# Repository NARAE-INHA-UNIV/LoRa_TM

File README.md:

# LoRa TM

DIY telemetry module based Ebyte LoRa.

- 활동명 : [UAV] DIY Telemerty Module
- 일시 : 2024 동계방학
- 팀명 : 항공전자 (구 FC)
- 팀장 : 
  - 송민우 (2024) : 개념 설계, 회로 설계
  - 이현제 (2025) : 회로 설계, 펌웨어 작성

## USB CDC

ST에서 제공하는 라이브러리 사용시 RAM, Flash memory 용량 초과.

[Making USB Device With STM32 + TinyUSB](https://ejaaskel.dev/making-usb-device-with-stm32-tinyusb/)

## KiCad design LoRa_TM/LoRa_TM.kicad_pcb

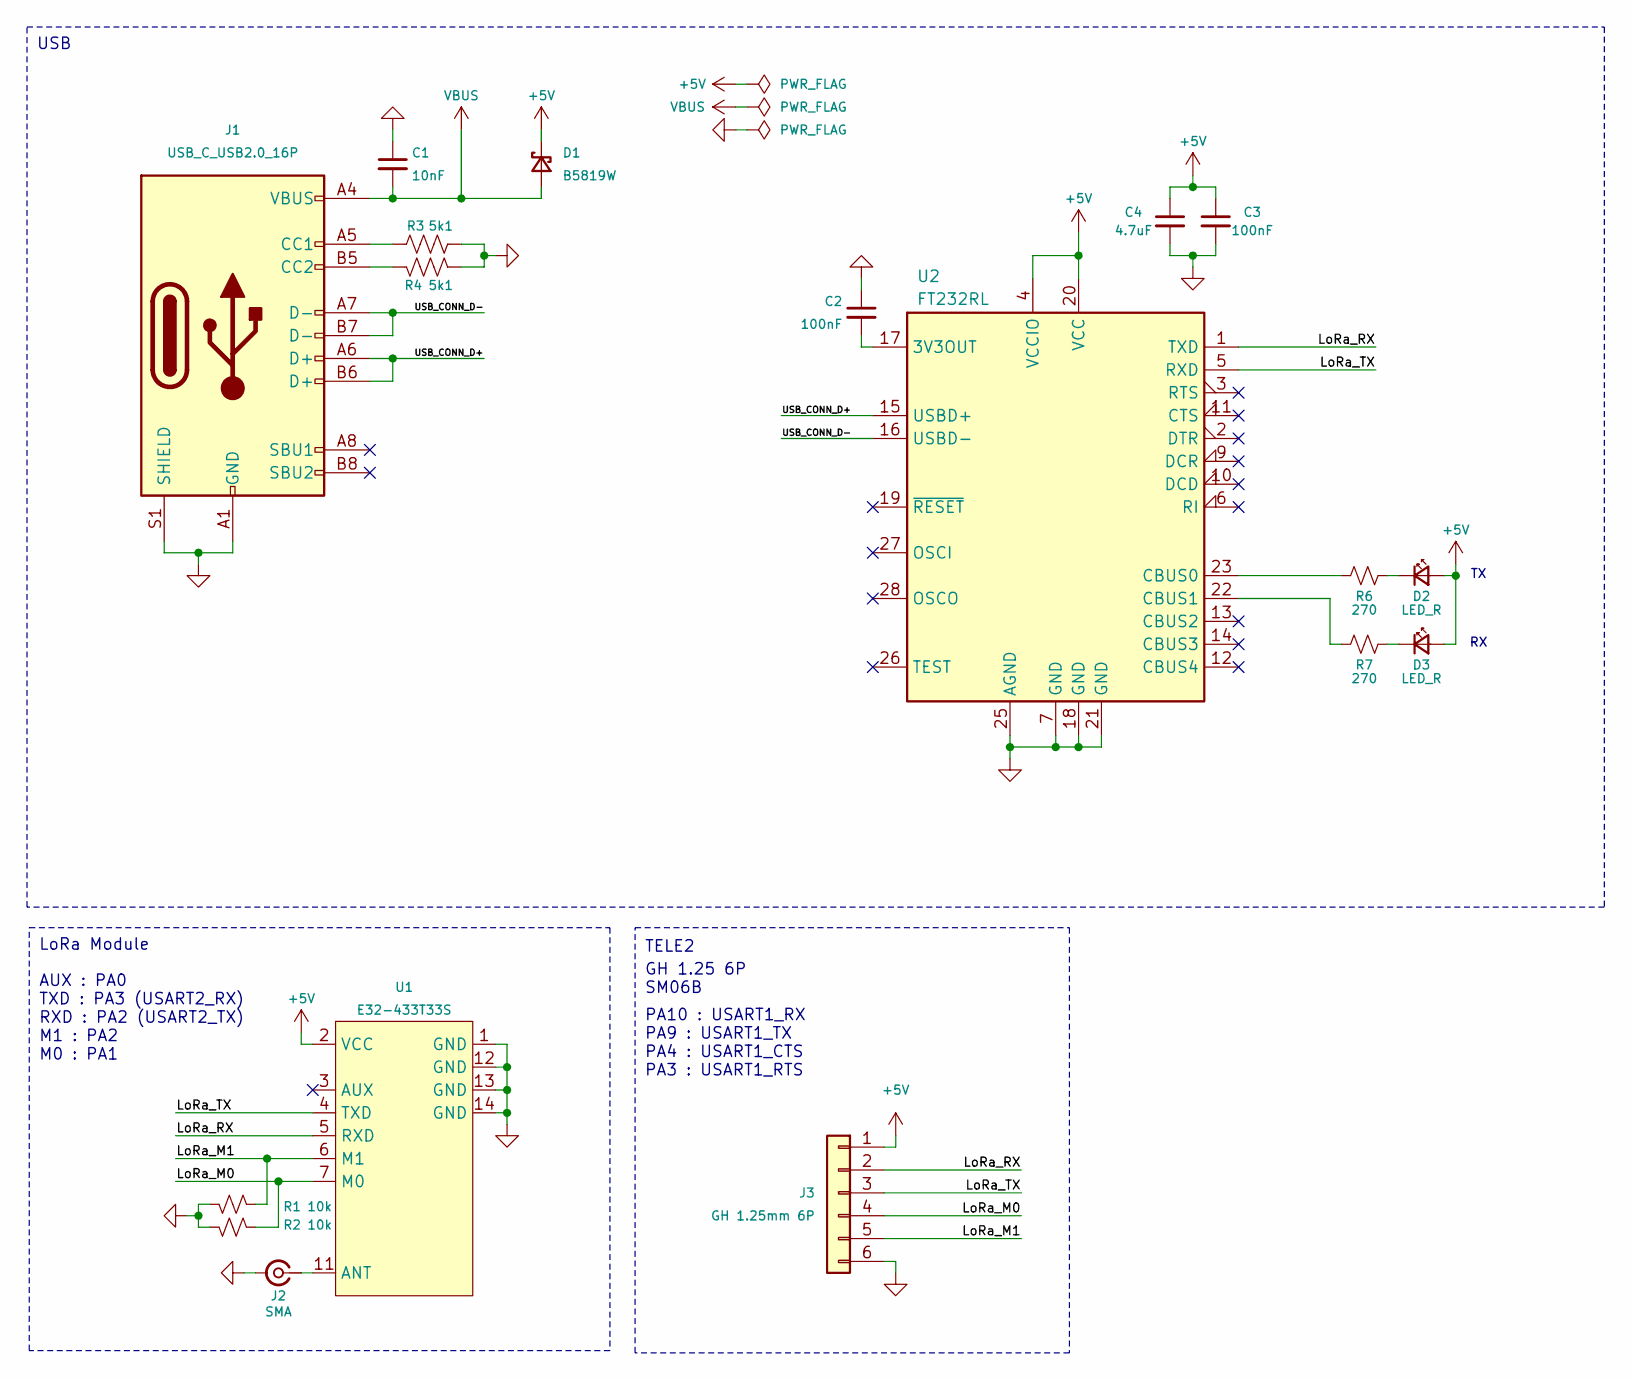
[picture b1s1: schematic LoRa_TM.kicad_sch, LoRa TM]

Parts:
C1: 10nF; C_0603_1608Metric; LCSC C1589
C2, C3: 100nF; C_0603_1608Metric; LCSC C1590
C4: 4.7uF; C_0603_1608Metric; LCSC C1705
D1: B5819W; D_SOD-323; LCSC C64885
D2, D3: LED_R; LED_0603_1608Metric; LCSC C2286
J1: USB_C_USB2.0_16P; USB_C_Receptacle_GCT_USB4105-xx-A_16P_TopMnt_Horizontal; LCSC C2765186
J2: SMA; SMA_EdgeMount; LCSC C376663
J3: GH 1.25mm 6P; JST_GH_SM06B-GHS-TB_06x1.25mm_Angled; LCSC C133065
R1, R2: 10k; R_0603_1608Metric; LCSC C15401
R3, R4: 5k1; R_0603_1608Metric; LCSC C14677
R6, R7: 270; R_0603_1608Metric; LCSC C22966
U1: E32-433T33S; E22-XXXT33S
U2: FT232RL; SSOP-28_5.3x10.2mm_P0.65mm; LCSC C8690

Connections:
+5V: C3.1, C4.1, D1.1 (K), D2.2 (A), D3.2 (A), J3.1, U1.2 (VCC), U2.4 (VCCIO), U2.20 (VCC)
/LoRa_M0: J3.4, R2.1, U1.7 (M0)
/LoRa_M1: J3.5, R1.1, U1.6 (M1)
/LoRa_RX: J3.2, U1.5 (RXD), U2.1 (TXD)
/LoRa_TX: J3.3, U1.4 (TXD), U2.5 (RXD)
/USB_CONN_D+: J1.A6 (D+), J1.B6 (D+), U2.15 (USBD+)
/USB_CONN_D-: J1.A7 (D-), J1.B7 (D-), U2.16 (USBD-)
GND: C1.1, C2.1, C3.2, C4.2, J1.A1 (GND), J1.A12 (GND), J1.B1 (GND), J1.B12 (GND), J1.S1 (SHIELD), J2.2 (Ext), J3.6, R1.2, R2.2, R3.2, R4.2, U1.1 (GND), U1.12 (GND), U1.13 (GND), U1.14 (GND), U2.7 (GND), U2.18 (GND), U2.21 (GND), U2.25 (AGND)
unnamed: D2.1 (K), R6.1
unnamed: D3.1 (K), R7.1
unnamed: J1.A5 (CC1), R3.1
unnamed: J1.B5 (CC2), R4.1
unnamed: J2.1 (In), U1.11 (ANT)
unnamed: C2.2, U2.17 (3V3OUT)
unnamed: R6.2, U2.23 (CBUS0)
unnamed: R7.2, U2.22 (CBUS1)
VBUS: C1.2, D1.2 (A), J1.A4 (VBUS), J1.A9 (VBUS), J1.B4 (VBUS), J1.B9 (VBUS)

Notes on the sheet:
TELE2
AUX : PA0 TXD : PA3 (USART2_RX) RXD : PA2 (USART2_TX) M1 : PA2 M0 : PA1
GH 1.25 6P SM06B
USB
PA10 : USART1_RX PA9 : USART1_TX PA4 : USART1_CTS PA3 : USART1_RTS
LoRa Module

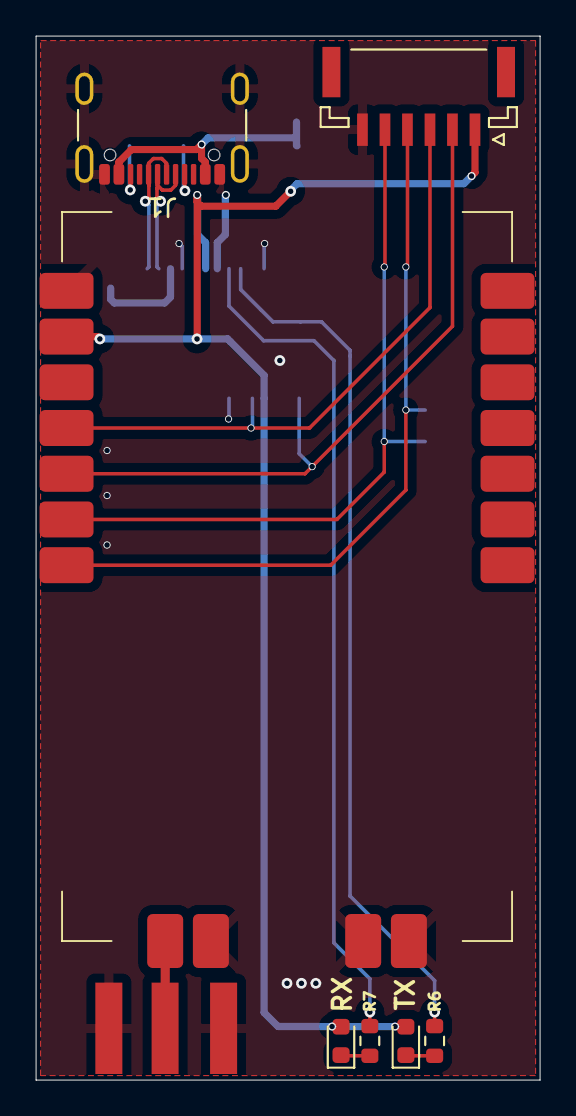
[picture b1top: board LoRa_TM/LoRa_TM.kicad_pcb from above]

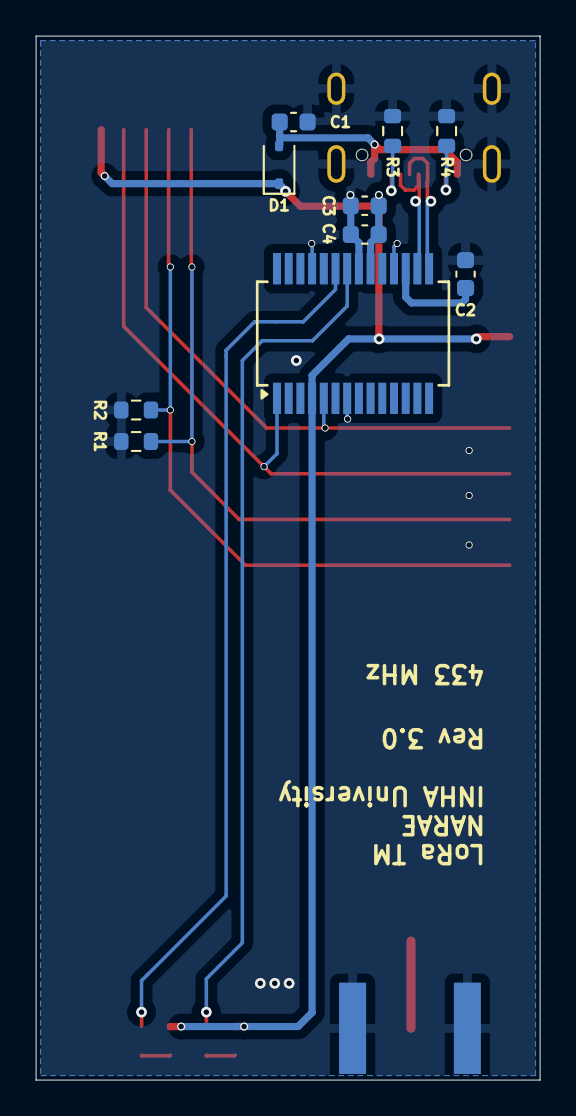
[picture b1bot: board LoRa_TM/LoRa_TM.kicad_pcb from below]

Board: 2 copper layers, 28.0 x 58.0 mm, 18 parts (10 on the bottom side), 17 nets.

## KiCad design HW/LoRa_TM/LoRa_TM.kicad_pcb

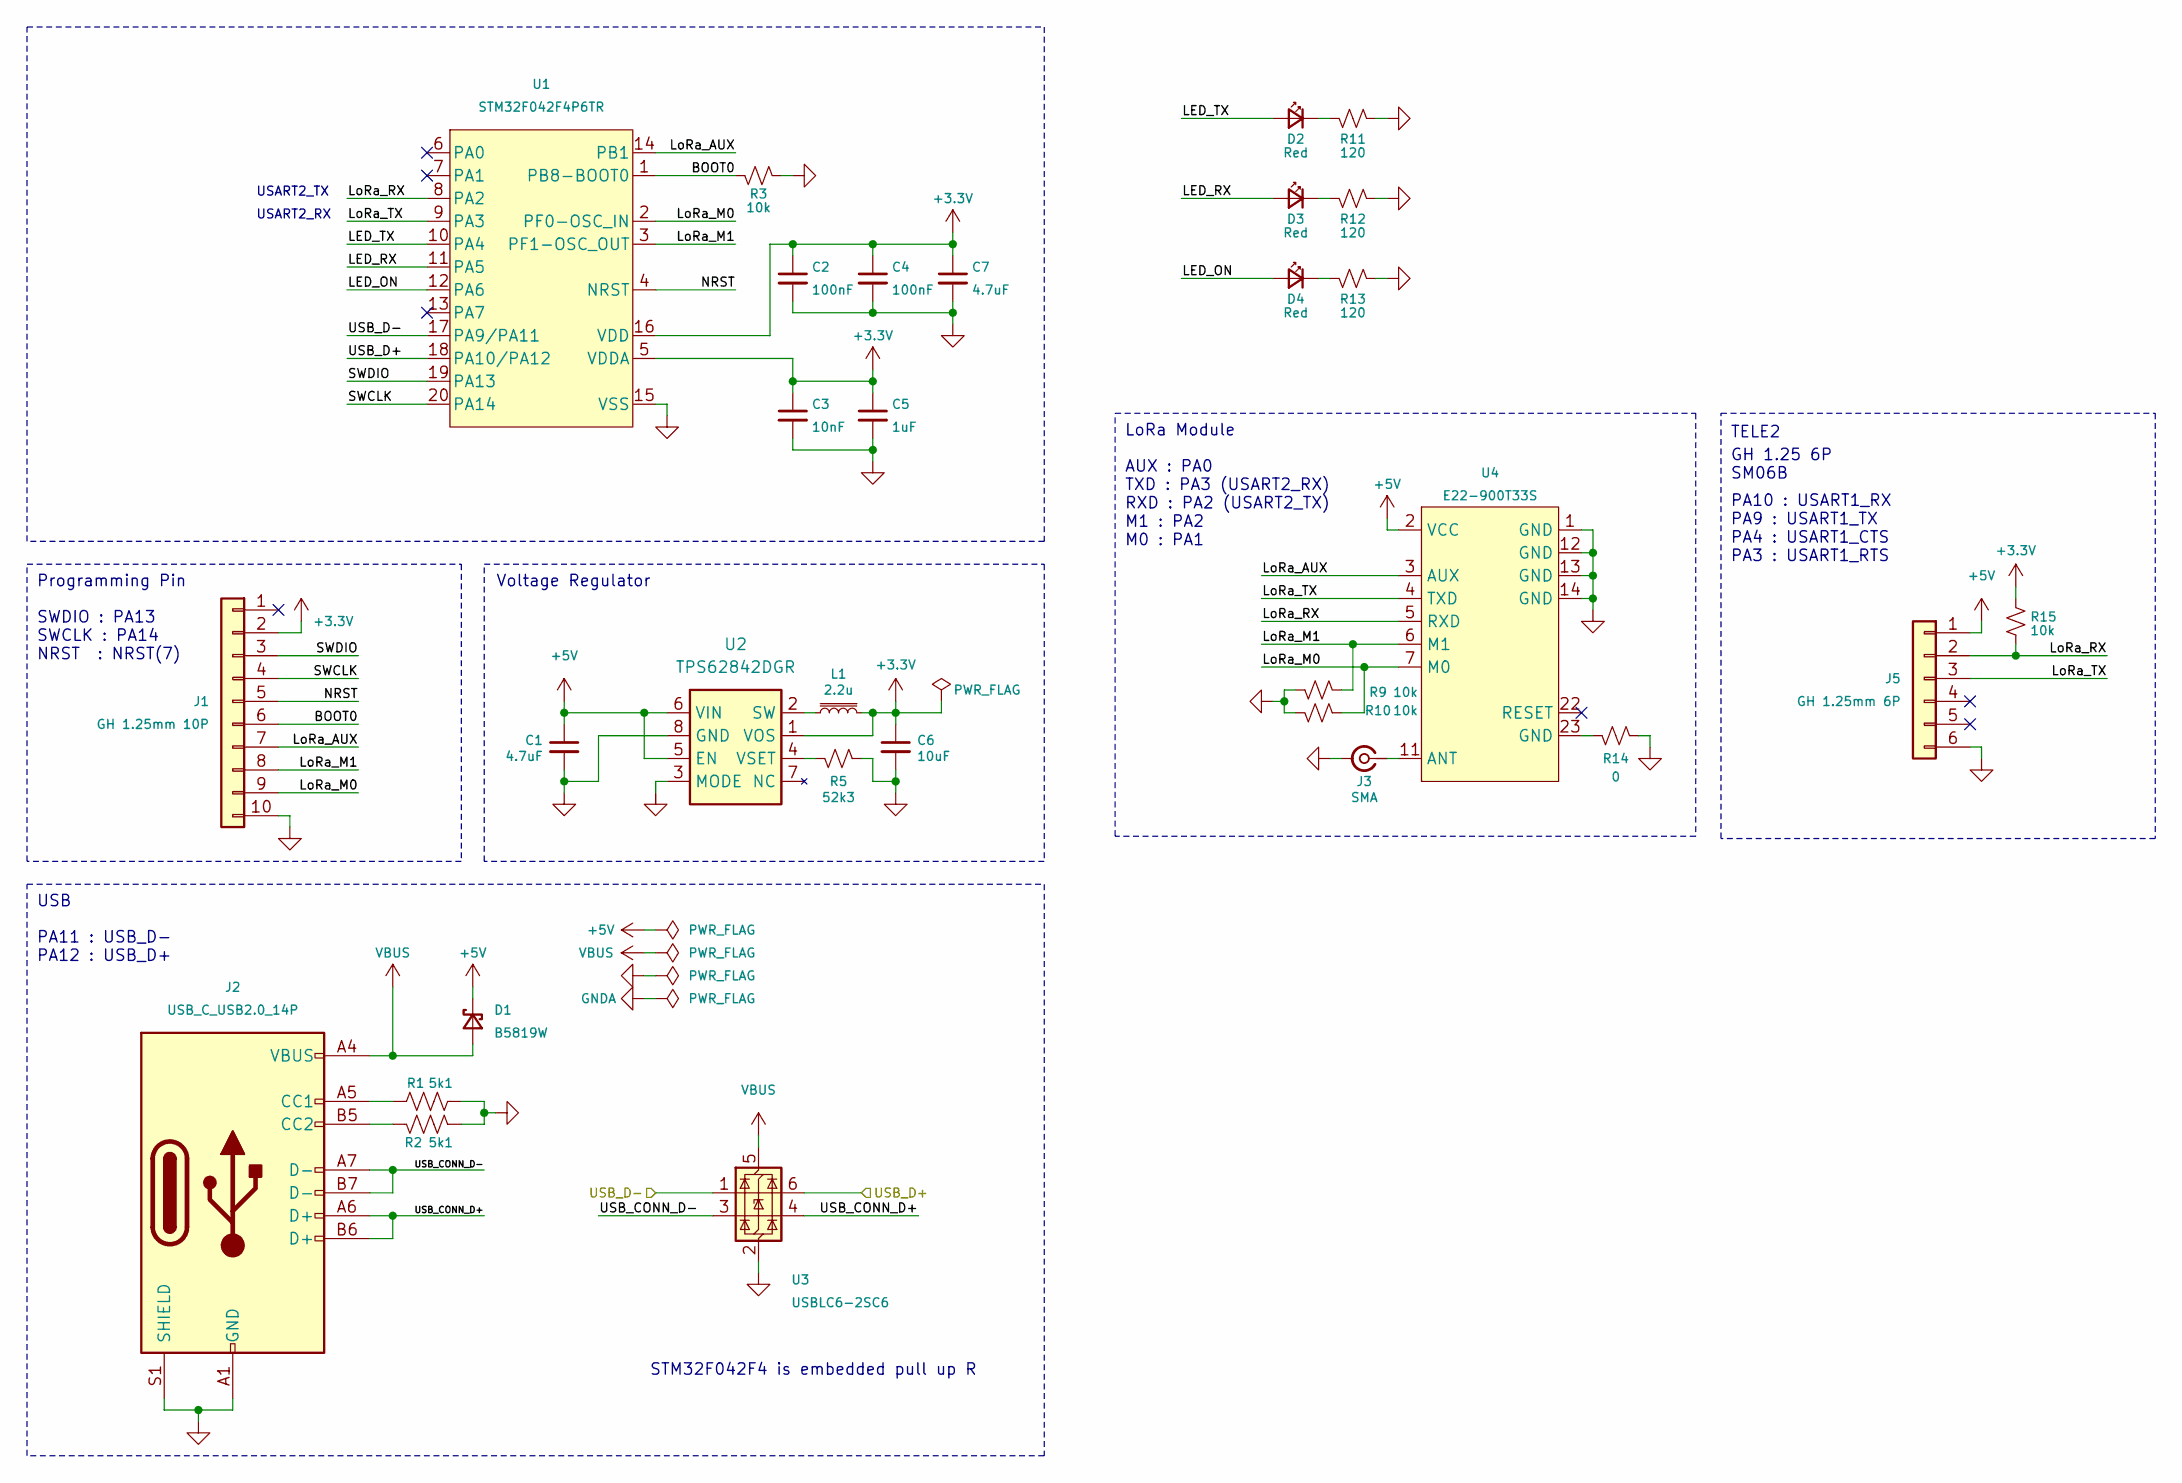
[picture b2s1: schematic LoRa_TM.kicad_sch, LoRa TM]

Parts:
C1, C7: 4.7uF; C_0603_1608Metric; LCSC C1705
C2, C4: 100nF; C_0603_1608Metric; LCSC C1590
C3: 10nF; C_0603_1608Metric; LCSC C1589
C5: 1uF; C_0603_1608Metric; LCSC C1592
C6: 10uF; C_0603_1608Metric; LCSC C1691
D1: B5819W; D_SOD-323; LCSC C64885
D2, D3, D4: Red; LED_0603_1608Metric; LCSC C2286
J1: GH 1.25mm 10P; JST_GH_SM10B-GHS-TB_10x1.25mm_Angled; LCSC C2683602
J2: USB_C_USB2.0_14P; USB_C_Receptacle_GCT_USB4110; LCSC C709031
J3: SMA; SMA_EdgeMount
J5: GH 1.25mm 6P; JST_GH_SM06B-GHS-TB_06x1.25mm_Angled; LCSC C133065
L1: 2.2u; VLS201610ET-2R2M
R1, R2: 5k1; R_0603_1608Metric; LCSC C14677
R3, R9, R10, R15: 10k; R_0603_1608Metric; LCSC C15401
R5: 52k3; R_0603_1608Metric
R11, R12, R13: 120; R_0603_1608Metric; LCSC C22787
R14: 0; R_0603_1608Metric; LCSC C15402
U1: STM32F042F4P6TR; TSSOP20; LCSC C81002
U2: TPS62842DGR; HVSSOP-8-1EP_3x3mm_P0.65mm_EP1.57x1.89mm; LCSC C2873354
U3: USBLC6-2SC6; SOT-23-6; LCSC C7519
U4: E22-900T33S; E22-XXXT33S

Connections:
+3.3V: C2.1, C3.1, C4.1, C5.1, C6.1, C7.1, J1.2, L1.2, R15.1, U1.5 (VDDA), U1.16 (VDD), U2.1 (VOS)
+5V: C1.1, D1.1 (K), J5.1, U2.5 (EN), U2.6 (VIN), U4.2 (VCC)
/BOOT0: J1.6, R3.2, U1.1 (PB8-BOOT0)
/LED_ON: D4.2 (A), U1.12 (PA6)
/LED_RX: D3.2 (A), U1.11 (PA5)
/LED_TX: D2.2 (A), U1.10 (PA4)
/LoRa_AUX: J1.7, U1.14 (PB1), U4.3 (AUX)
/LoRa_M0: J1.9, R10.1, U1.2 (PF0-OSC_IN), U4.7 (M0)
/LoRa_M1: J1.8, R9.1, U1.3 (PF1-OSC_OUT), U4.6 (M1)
/LoRa_RX: J5.2, R15.2, U1.8 (PA2), U4.5 (RXD)
/LoRa_TX: J5.3, U1.9 (PA3), U4.4 (TXD)
/NRST: J1.5, U1.4 (NRST)
/SWCLK: J1.4, U1.20 (PA14)
/SWDIO: J1.3, U1.19 (PA13)
/USB_CONN_D+: J2.A6 (D+), J2.B6 (D+), U3.4 (I/O2)
/USB_CONN_D-: J2.A7 (D-), J2.B7 (D-), U3.3 (I/O2)
/USB_D+: U1.18 (PA10/PA12), U3.6 (I/O1)
/USB_D-: U1.17 (PA9/PA11), U3.1 (I/O1)
GND: C1.2, C2.2, C3.2, C4.2, C5.2, C6.2, C7.2, J1.10, J2.A1 (GND), J2.A12 (GND), J2.B1 (GND), J2.B12 (GND), J2.S1 (SHIELD), J3.2 (Ext), J5.6, R1.2, R2.2, R3.1, R5.1, R9.2, R10.2, R11.2, R12.2, R13.2, R14.1, U1.15 (VSS), U2.3 (MODE), U2.8 (GND), U3.2 (GND), U4.1 (GND), U4.12 (GND), U4.13 (GND), U4.14 (GND)
unnamed: D2.1 (K), R11.1
unnamed: D3.1 (K), R12.1
unnamed: D4.1 (K), R13.1
unnamed: J2.A5 (CC1), R1.1
unnamed: J2.B5 (CC2), R2.1
unnamed: J3.1 (In), U4.11 (ANT)
unnamed: R14.2, U4.23 (GND)
unnamed: L1.1, U2.2 (SW)
unnamed: R5.2, U2.4 (VSET)
VBUS: D1.2 (A), J2.A4 (VBUS), J2.A9 (VBUS), J2.B4 (VBUS), J2.B9 (VBUS), U3.5 (VBUS)

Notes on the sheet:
TELE2
STM32F042F4 is embedded pull up R
SWDIO : PA13 SWCLK : PA14 NRST : NRST(7)
AUX : PA0 TXD : PA3 (USART2_RX) RXD : PA2 (USART2_TX) M1 : PA2 M0 : PA1
USART2_RX
PA11 : USB_D- PA12 : USB_D+
Voltage Regulator
GH 1.25 6P SM06B
USB
USART2_TX
PA10 : USART1_RX PA9 : USART1_TX PA4 : USART1_CTS PA3 : USART1_RTS
LoRa Module
Programming Pin

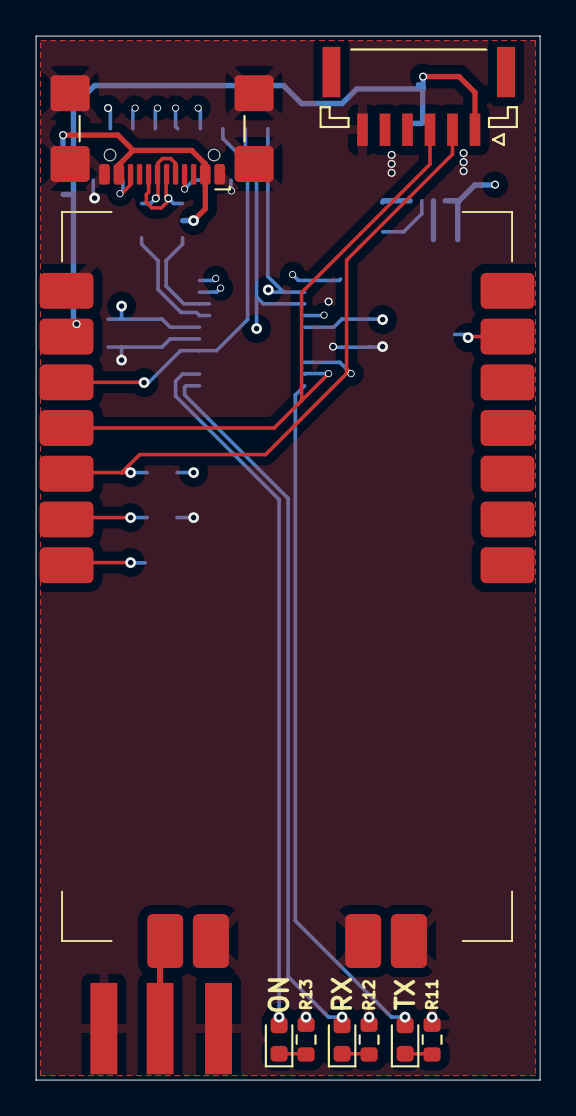
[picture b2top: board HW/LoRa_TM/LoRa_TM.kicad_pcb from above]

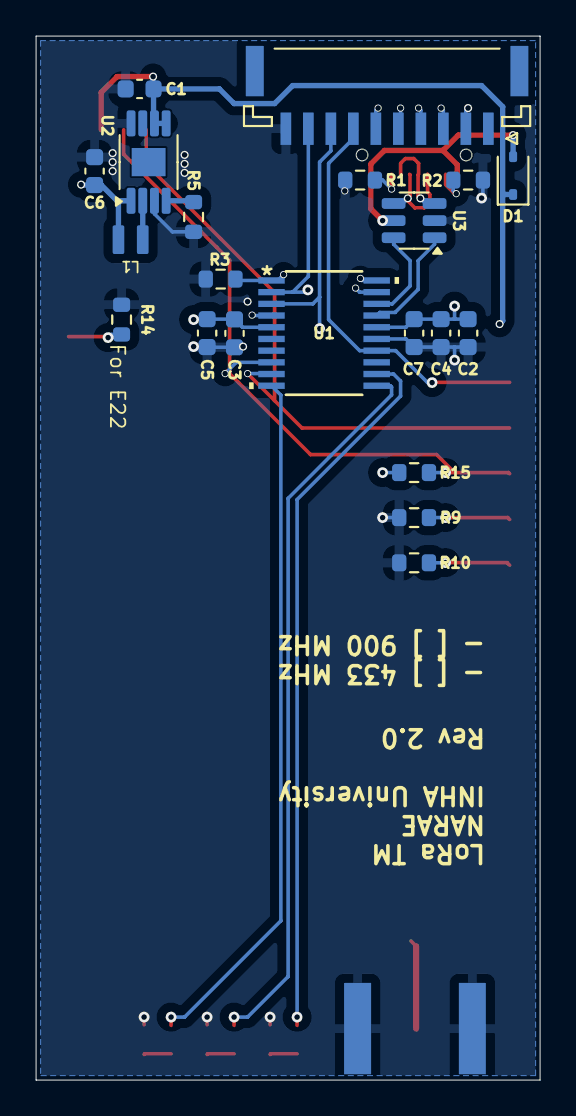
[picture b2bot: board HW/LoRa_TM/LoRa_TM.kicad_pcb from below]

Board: 4 copper layers, 28.0 x 58.0 mm, 31 parts (21 on the bottom side), 29 nets.

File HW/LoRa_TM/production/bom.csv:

Designator,Footprint,Quantity,Value,LCSC Part #
C1,0603,1,4.7uF,C307423
"C2, C4",0603,2,100nF,C1525
C3,0603,1,10nF,C1525
C5,0603,1,1uF,C1525
C6,0603,1,10uF,C307415
C7,0603,1,4.7uF,C1525
D1,D_SOD-323,1,B5819W,C22624
"D2, D3, D4",0603,3,Red,C130719
J1,JST_GH_SM10B-GHS-TB_10x1.25mm_Angled,1,GH 1.25mm 10P,C133065
J2,USB_C_Receptacle_GCT_USB4110,1,USB_C_USB2.0_14P,C709031
J3,SMA_EdgeMount,1,SMA,
J5,JST_GH_SM06B-GHS-TB_06x1.25mm_Angled,1,GH 1.25mm 6P,C133065
L1,VLS201610ET-2R2M,1,2.2u,C114768
"R1, R2",0603,2,5k1,C25905
"R10, R3, R9",0603,3,10k, C25079
"R11, R12, R13",0603,3,120, C25079
R14,0603,1,0, C25079
R15,0603,1,10k,C25531
R5,0603,1,52k3,C2998050
U1,TSSOP20,1,STM32F042F4P6TR,
U2,HVSSOP-8-1EP_3x3mm_P0.65mm_EP1.57x1.89mm,1,TPS62842DGR,
U3,SOT-23-6,1,USBLC6-2SC6,C7519
U4,E22-XXXT33S,1,E22-900T33S,

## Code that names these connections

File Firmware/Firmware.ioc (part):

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Mcu.Name=STM32F042F4Px
Mcu.Package=TSSOP20
Mcu.UserName=STM32F042F4Px
PA11.Mode=Device
PA11.Signal=USB_DM
PA12.Mode=Device
PA12.Signal=USB_DP
PA13.Mode=Serial_Wire
PA13.Signal=SYS_SWDIO
PA14.Mode=Serial_Wire
PA14.Signal=SYS_SWCLK
PA2.GPIOParameters=GPIO_Label
PA2.GPIO_Label=LoRa_RX
PA2.Mode=Asynchronous
PA2.Signal=USART2_TX
PA3.GPIOParameters=GPIO_Label
PA3.GPIO_Label=LoRa_TX
PA3.Mode=Asynchronous
PA3.Signal=USART2_RX
PA4.GPIOParameters=GPIO_Label
PA4.GPIO_Label=LED_TX
PA4.Signal=GPIO_Output
PA5.GPIOParameters=GPIO_Label
PA5.GPIO_Label=LED_RX
PA5.Signal=GPIO_Output
PA6.GPIOParameters=GPIO_Label
PA6.GPIO_Label=LED_ON
PA6.Signal=GPIO_Output
PB1.GPIOParameters=GPIO_Label
PB1.GPIO_Label=LoRa_AUX
PB1.Signal=GPIO_Input
PF0-OSC_IN.GPIOParameters=GPIO_Label
PF0-OSC_IN.GPIO_Label=LoRa_M0
PF0-OSC_IN.Signal=GPIO_Output
PF1-OSC_OUT.GPIOParameters=GPIO_Label
PF1-OSC_OUT.GPIO_Label=LoRa_M1
PF1-OSC_OUT.Signal=GPIO_Output
RCC.SYSCLKFreq_VALUE=48000000
RCC.SYSCLKSource=RCC_SYSCLKSOURCE_HSI48
board=custom

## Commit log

2025-06-13 Schematic Done
2025-06-18 stm32u375 update
2025-06-18 PCB Done
2025-06-18 Schematic update
2025-06-19 minor fix
2025-07-03 Firmware ioc setup
2025-08-30 version 3
